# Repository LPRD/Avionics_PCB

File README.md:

# Avionics_PCB
EAGLE Board and schematic files

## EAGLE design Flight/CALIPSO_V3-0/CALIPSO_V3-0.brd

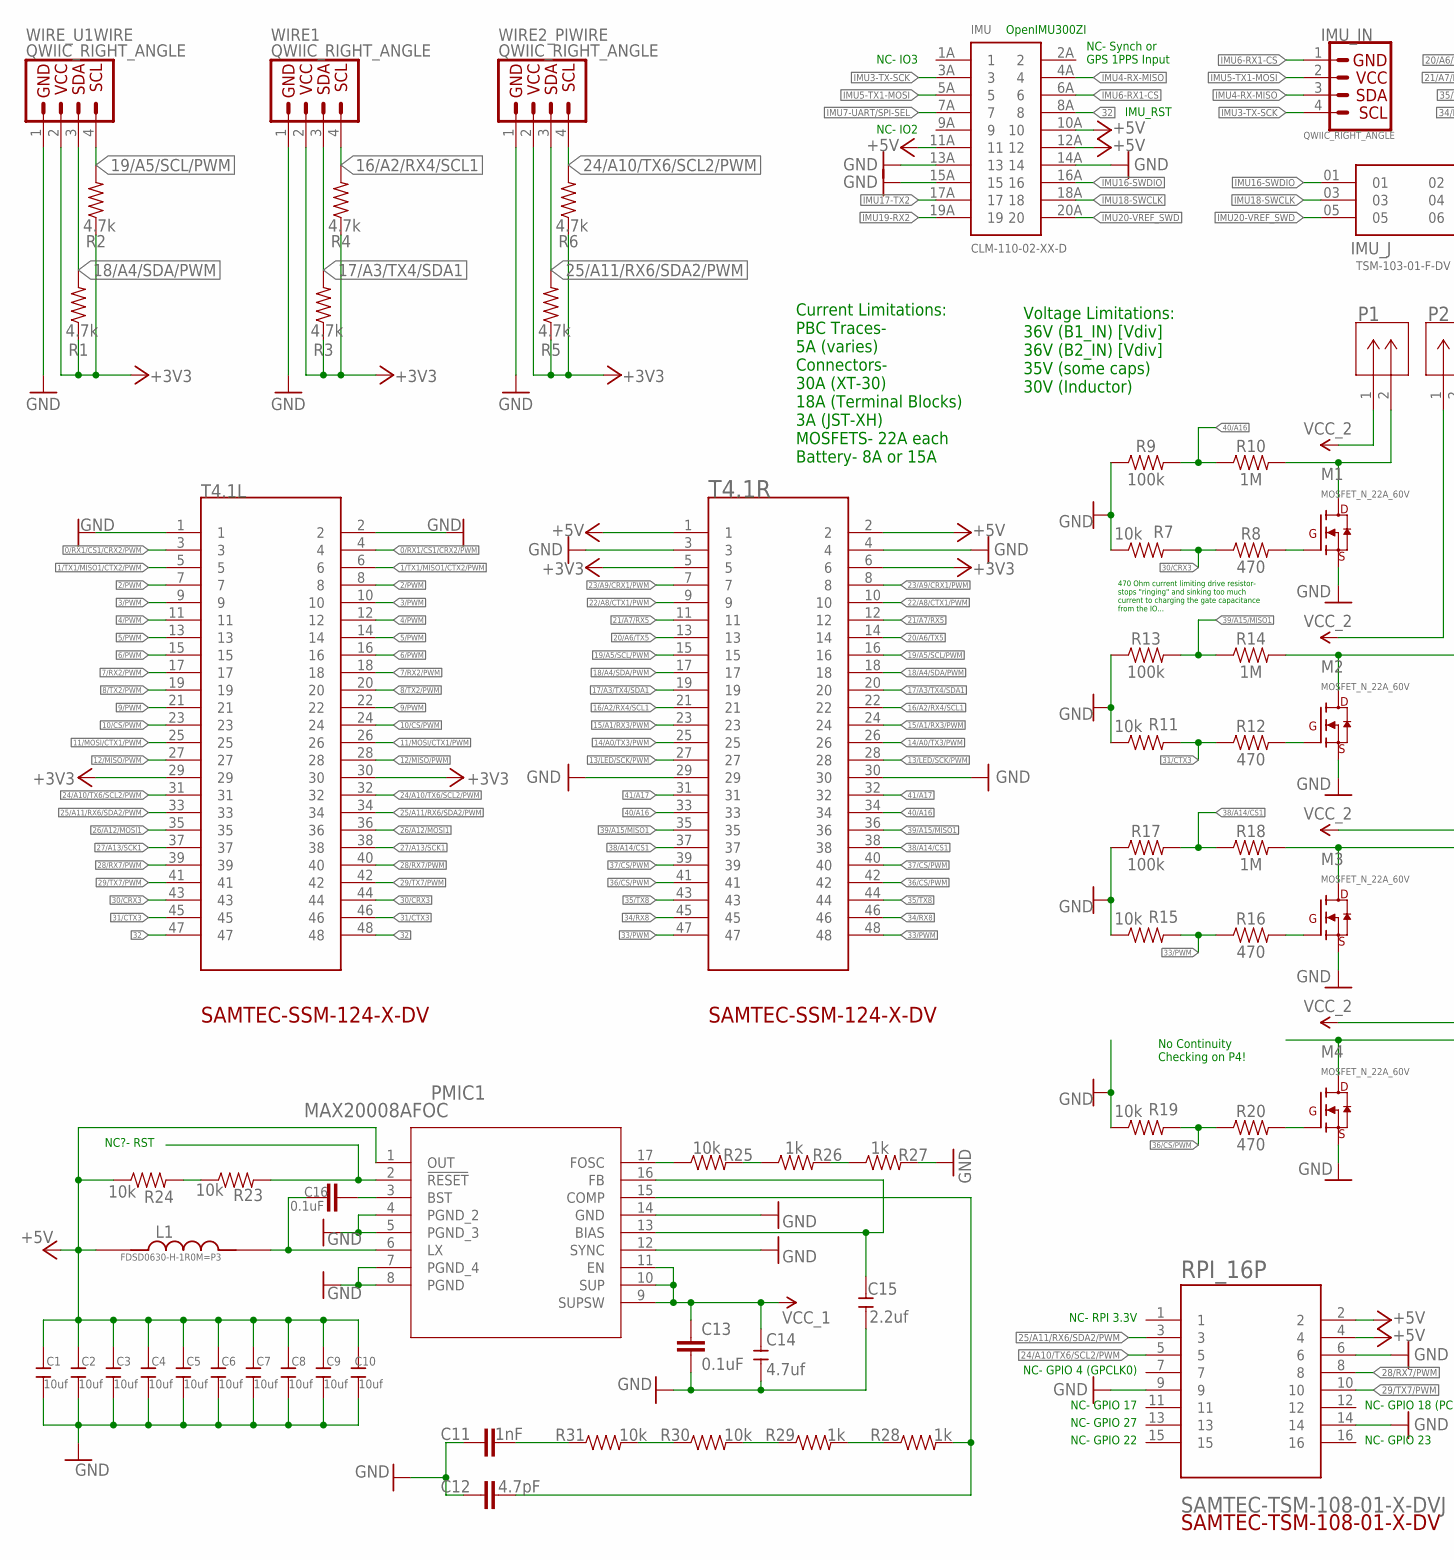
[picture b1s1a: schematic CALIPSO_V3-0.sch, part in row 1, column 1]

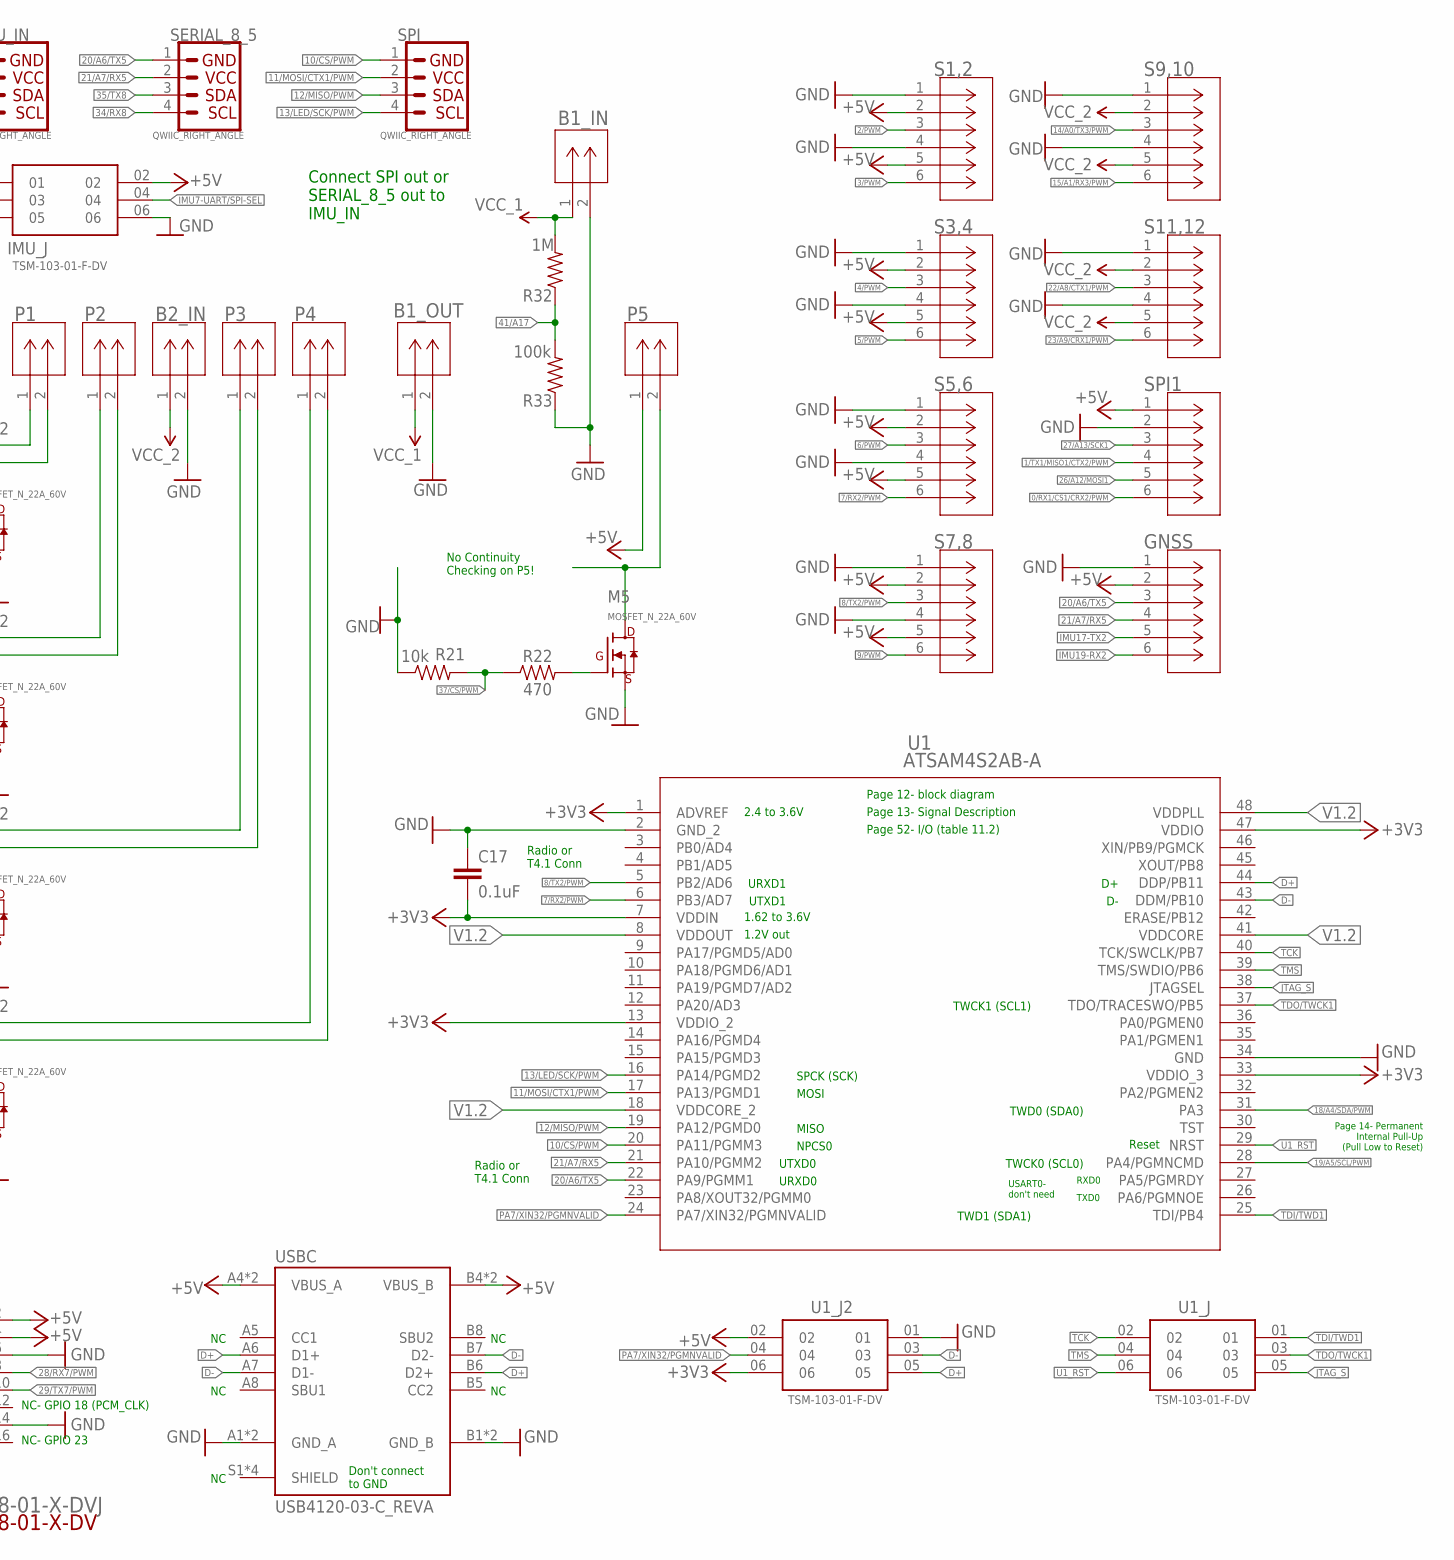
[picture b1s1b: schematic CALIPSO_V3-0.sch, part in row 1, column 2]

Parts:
B1_IN, B1_OUT, B2_IN: TERMINAL_BLOCK_5MM_2P; TB_2P
C1, C2, C3, C4, C5, C6, C7, C8, C9, C10: 10uf; C1206
C11: 1nF; 0603
C12: 4.7pF; 0603
C13, C16, C17: 0.1uF; 0603
C14: 4.7uf; C0805
C15: 2.2uf; C0805
GNSS: JST-S6B-SH_DEV; JST-S6B-XH
IMU: CLM-110-02-XX-D; CLM-110-02-XX-D_MOD
IMU_IN: QWIIC_RIGHT_ANGLE; JST04_1MM_RA
IMU_J: TSM-103-01-F-DV; SAMTEC_TSM-103-01-F-DV
L1: FDSD0630-H-1R0M=P3; IND_FDSD0630-H-1R0M=P3
M1, M2, M3, M4, M5: MOSFET_N_22A_60V; SOT-669_LFPAK56_POWERSO8
P1, P2, P3, P4, P5: TERMINAL_BLOCK_5MM_2P; TB_2P
PMIC1: MAX20008AFOC; MAX20008AFOC_17QFN
R1, R2, R3, R4, R5, R6: 4.7k; 0603
R7, R11, R15, R19, R21, R23, R24, R25, R30, R31: 10k; 0603
R8, R12, R16, R20, R22: 470; 0603
R9, R13, R17, R33: 100k; 0603
R10, R14, R18, R32: 1M; 0603
R26, R27, R28, R29: 1k; 0603
RPI_16P: SAMTEC-TSM-108-01-X-DVJ; SAMTEC-TSM-108-01-X-DV
S1,2, S3,4, S5,6, S7,8, S9,10, S11,12: JST-S6B-SH_DEV; JST-S6B-XH
SERIAL_8_5: QWIIC_RIGHT_ANGLE; JST04_1MM_RA
SPI: QWIIC_RIGHT_ANGLE; JST04_1MM_RA
SPI1: JST-S6B-SH_DEV; JST-S6B-XH
T4.1L, T4.1R: SAMTEC-SSM-124-X-DVJ; SAMTEC-SSM-124-X-DV
U1: ATSAM4S2AB-A; ATSAM4S2AB-A_48-LQFP
U1_J, U1_J2: TSM-103-01-F-DV; SAMTEC_TSM-103-01-F-DV
USBC: USB4120-03-C_REVA; GCT_USB4120-03-C_REVA
WIRE1, WIRE2_PIWIRE: QWIIC_RIGHT_ANGLE; JST04_1MM_RA
WIRE_U1WIRE: QWIIC_RIGHT_ANGLE; JST04_1MM_RA

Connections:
0/RX1/CS1/CRX2/PWM: SPI1.6, T4.1L.3, T4.1L.4
1/TX1/MISO1/CTX2/PWM: SPI1.4, T4.1L.5, T4.1L.6
2/PWM: S1,2.3, T4.1L.7, T4.1L.8
3/PWM: S1,2.6, T4.1L.9, T4.1L.10
4/PWM: S3,4.3, T4.1L.11, T4.1L.12
5/PWM: S3,4.6, T4.1L.13, T4.1L.14
6/PWM: S5,6.3, T4.1L.15, T4.1L.16
7/RX2/PWM: S5,6.6, T4.1L.17, T4.1L.18, U1.6 (PB3/AD7)
8/TX2/PWM: S7,8.3, T4.1L.19, T4.1L.20, U1.5 (PB2/AD6)
9/PWM: S7,8.6, T4.1L.21, T4.1L.22
10/CS/PWM: SPI.1, T4.1L.23, T4.1L.24, U1.20 (PA11/PGMM3)
11/MOSI/CTX1/PWM: SPI.2, T4.1L.25, T4.1L.26, U1.17 (PA13/PGMD1)
12/MISO/PWM: SPI.3, T4.1L.27, T4.1L.28, U1.19 (PA12/PGMD0)
13/LED/SCK/PWM: SPI.4, T4.1R.27, T4.1R.28, U1.16 (PA14/PGMD2)
14/A0/TX3/PWM: S9,10.3, T4.1R.25, T4.1R.26
15/A1/RX3/PWM: S9,10.6, T4.1R.23, T4.1R.24
16/A2/RX4/SCL1: R4.2, T4.1R.21, T4.1R.22, WIRE1.4
17/A3/TX4/SDA1: R3.2, T4.1R.19, T4.1R.20, WIRE1.3
18/A4/SDA/PWM: R1.2, T4.1R.17, T4.1R.18, U1.31 (PA3), WIRE_U1WIRE.3
19/A5/SCL/PWM: R2.2, T4.1R.15, T4.1R.16, U1.28 (PA4/PGMNCMD), WIRE_U1WIRE.4
20/A6/TX5: GNSS.3, SERIAL_8_5.1, T4.1R.13, T4.1R.14, U1.22 (PA9/PGMM1)
21/A7/RX5: GNSS.4, SERIAL_8_5.2, T4.1R.11, T4.1R.12, U1.21 (PA10/PGMM2)
22/A8/CTX1/PWM: S11,12.3, T4.1R.9, T4.1R.10
23/A9/CRX1/PWM: S11,12.6, T4.1R.7, T4.1R.8
24/A10/TX6/SCL2/PWM: R6.2, RPI_16P.5, T4.1L.31, T4.1L.32, WIRE2_PIWIRE.4
25/A11/RX6/SDA2/PWM: R5.2, RPI_16P.3, T4.1L.33, T4.1L.34, WIRE2_PIWIRE.3
26/A12/MOSI1: SPI1.5, T4.1L.35, T4.1L.36
27/A13/SCK1: SPI1.3, T4.1L.37, T4.1L.38
28/RX7/PWM: RPI_16P.8, T4.1L.39, T4.1L.40
29/TX7/PWM: RPI_16P.10, T4.1L.41, T4.1L.42
30/CRX3: R7.2, R8.1, T4.1L.43, T4.1L.44
31/CTX3: R11.2, R12.1, T4.1L.45, T4.1L.46
32: IMU.8A (8), T4.1L.47, T4.1L.48
33/PWM: R15.2, R16.1, T4.1R.47, T4.1R.48
34/RX8: SERIAL_8_5.4, T4.1R.45, T4.1R.46
35/TX8: SERIAL_8_5.3, T4.1R.43, T4.1R.44
36/CS/PWM: R19.2, R20.1, T4.1R.41, T4.1R.42
37/CS/PWM: R21.2, R22.1, T4.1R.39, T4.1R.40
38/A14/CS1: R17.2, R18.1, T4.1R.37, T4.1R.38
39/A15/MISO1: R13.2, R14.1, T4.1R.35, T4.1R.36
40/A16: R9.2, R10.1, T4.1R.33, T4.1R.34
41/A17: R32.1, R33.2, T4.1R.31, T4.1R.32
+3V3: C17.2, R1.1, R2.1, R3.1, R4.1, R5.1, R6.1, T4.1L.29, T4.1L.30, T4.1R.5, T4.1R.6, U1.1 (ADVREF), U1.7 (VDDIN), U1.13 (VDDIO_2), U1.33 (VDDIO_3), U1.47 (VDDIO), U1_J2.06, WIRE1.2, WIRE2_PIWIRE.2, WIRE_U1WIRE.2
+5V: C1.2, C2.2, C3.2, C4.2, C5.2, C6.2, C7.2, C8.2, C9.2, C10.2, GNSS.2, IMU.10A (10), IMU.11A (11), IMU.12A (12), IMU_J.02, L1.1, P5.1, PMIC1.1 (OUT), R24.1, RPI_16P.2, RPI_16P.4, S1,2.2, S1,2.5, S3,4.2, S3,4.5, S5,6.2, S5,6.5, S7,8.2, S7,8.5, SPI1.1, T4.1R.1, T4.1R.2, U1_J2.02, USBC.A4 (VBUS_A), USBC.A9 (VBUS_A), USBC.B4 (VBUS_B), USBC.B9 (VBUS_B)
BIAS/FB: C15.1, PMIC1.13 (BIAS), PMIC1.16 (FB)
BST: C16.2, PMIC1.3 (BST)
BUCK_RST: PMIC1.2 (!RESET), R23.2
COMP: C12.2, PMIC1.15 (COMP), R28.2
D+: U1.44 (DDP/PB11), U1_J2.05, USBC.A6 (D1+), USBC.B6 (D2+)
D-: U1.43 (DDM/PB10), U1_J2.03, USBC.A7 (D1-), USBC.B7 (D2-)
FOSC: PMIC1.17 (FOSC), R25.1
GND: B1_IN.2, B1_OUT.2, B2_IN.2, C1.1, C2.1, C3.1, C4.1, C5.1, C6.1, C7.1, C8.1, C9.1, C10.1, C11.1, C12.1, C13.2, C14.2, C15.2, C17.1, GNSS.1, IMU.13A (13), IMU.14A (14), IMU.15A (15), IMU_J.06, M1.1 (S), M1.2 (S), M1.3 (S), M2.1 (S), M2.2 (S), M2.3 (S), M3.1 (S), M3.2 (S), M3.3 (S), M4.1 (S), M4.2 (S), M4.3 (S), M5.1 (S), M5.2 (S), M5.3 (S), PMIC1.4 (PGND_2), PMIC1.5 (PGND_3), PMIC1.7 (PGND_4), PMIC1.8 (PGND), PMIC1.12 (SYNC), PMIC1.14 (GND), R7.1, R9.1, R11.1, R13.1, R15.1, R17.1, R19.1, R21.1, R27.2, R33.1, RPI_16P.6, RPI_16P.9, RPI_16P.14, S1,2.1, S1,2.4, S3,4.1, S3,4.4, S5,6.1, S5,6.4, S7,8.1, S7,8.4, S9,10.1, S9,10.4, S11,12.1, S11,12.4, SPI1.2, T4.1L.1, T4.1L.2, T4.1R.3, T4.1R.4, T4.1R.29, T4.1R.30, U1.2 (GND_2), U1.34 (GND), U1_J2.01, USBC.A1 (GND_A), USBC.A12 (GND_A), USBC.B1 (GND_B), USBC.B12 (GND_B), WIRE1.1, WIRE2_PIWIRE.1, WIRE_U1WIRE.1
IMU3-TX-SCK: IMU.3A (3), IMU_IN.4
IMU4-RX-MISO: IMU.4A (4), IMU_IN.3
IMU5-TX1-MOSI: IMU.5A (5), IMU_IN.2
IMU6-RX1-CS: IMU.6A (6), IMU_IN.1
IMU7-UART/SPI-SEL: IMU.7A (7), IMU_J.04
IMU16-SWDIO: IMU.16A (16), IMU_J.01
IMU17-TX2: GNSS.5, IMU.17A (17)
IMU18-SWCLK: IMU.18A (18), IMU_J.03
IMU19-RX2: GNSS.6, IMU.19A (19)
IMU20-VREF_SWD: IMU.20A (20), IMU_J.05
JTAG_S: U1.38 (JTAGSEL), U1_J.05
LX: C16.1, L1.2, PMIC1.6 (LX)
unnamed: M1.4 (G), R8.2
unnamed: M5.4 (G), R22.2
unnamed: R23.1, R24.2
unnamed: M2.4 (G), R12.2
unnamed: R25.2, R26.1
unnamed: R26.2, R27.1
unnamed: R30.1, R31.2
unnamed: R29.1, R30.2
unnamed: R28.1, R29.2
unnamed: M3.4 (G), R16.2
unnamed: C11.2, R31.1
unnamed: M4.4 (G), R20.2
P1D: M1.5 (D), P1.2, R10.2
P2D: M2.5 (D), P2.2, R14.2
P3D: M3.5 (D), P3.2, R18.2
P4D: M4.5 (D), P4.2
P5D: M5.5 (D), P5.2
PA7/XIN32/PGMNVALID: U1.24 (PA7/XIN32/PGMNVALID), U1_J2.04
TCK: U1.40 (TCK/SWCLK/PB7), U1_J.02
TDI/TWD1: U1.25 (TDI/PB4), U1_J.01
TDO/TWCK1: U1.37 (TDO/TRACESWO/PB5), U1_J.03
TMS: U1.39 (TMS/SWDIO/PB6), U1_J.04
U1_RST: U1.29 (NRST), U1_J.06
V1.2: U1.8 (VDDOUT), U1.18 (VDDCORE_2), U1.41 (VDDCORE), U1.48 (VDDPLL)
VCC_1: B1_IN.1, B1_OUT.1, C13.1, C14.1, PMIC1.9 (SUPSW), PMIC1.10 (SUP), PMIC1.11 (EN), R32.2
VCC_2: B2_IN.1, P1.1, P2.1, P3.1, P4.1, S9,10.2, S9,10.5, S11,12.2, S11,12.5

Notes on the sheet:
Current Limitations: PBC Traces- 5A (varies) Connectors- 30A (XT-30) 18A (Terminal Blocks) 3A (JST-XH) MOSFETS- 22A each Battery- 8A or 15A
470 Ohm current limiting drive resistor- stops "ringing" and sinking too much current to charging the gate capacitance from the IO...
Connect SPI out or SERIAL_8_5 out to IMU_IN
IMU_RST
NC- Synch or GPS 1PPS Input
NC- IO3
NC- IO2
NC- RPI 3.3V
NC- GPIO 4 (GPCLK0)
NC- GPIO 17
NC- GPIO 27
NC- GPIO 22
NC- GPIO 18 (PCM_CLK)
NC- GPIO 23
No Continuity Checking on P4!
No Continuity Checking on P5!
NC?- RST
Voltage Limitations: 36V (B1_IN) [Vdiv] 36V (B2_IN) [Vdiv] 35V (some caps) 30V (Inductor)
2.4 to 3.6V
1.2V out
1.62 to 3.6V
Reset
Page 52- I/O (table 11.2)
RXD0
TXD0
URXD0
UTXD0
URXD1
UTXD1
Page 12- block diagram
USART0- don't need
TWD0 (SDA0)
TWCK0 (SCL0)
TWD1 (SDA1)
TWCK1 (SCL1)
NPCS0
MISO
MOSI
SPCK (SCK)
Page 13- Signal Description

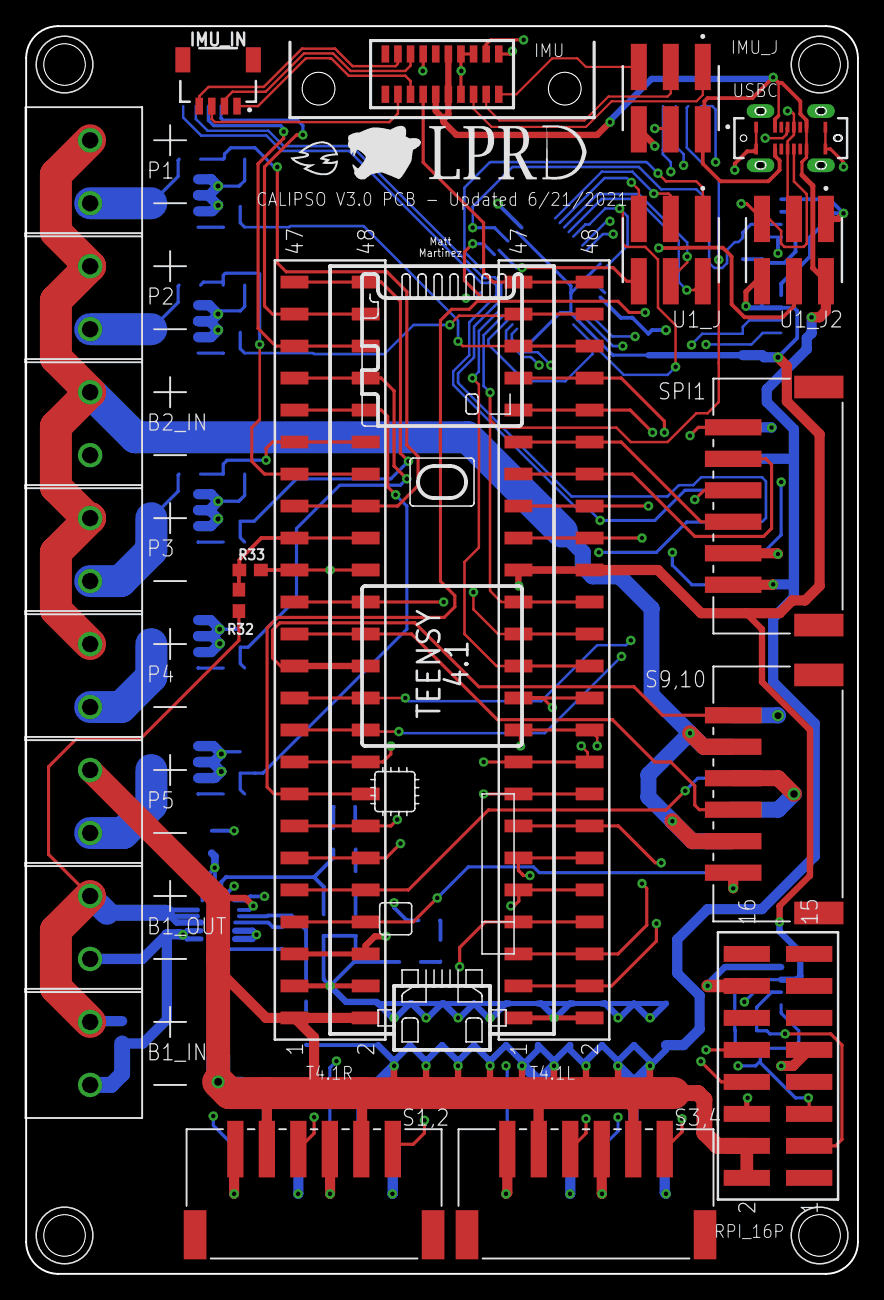
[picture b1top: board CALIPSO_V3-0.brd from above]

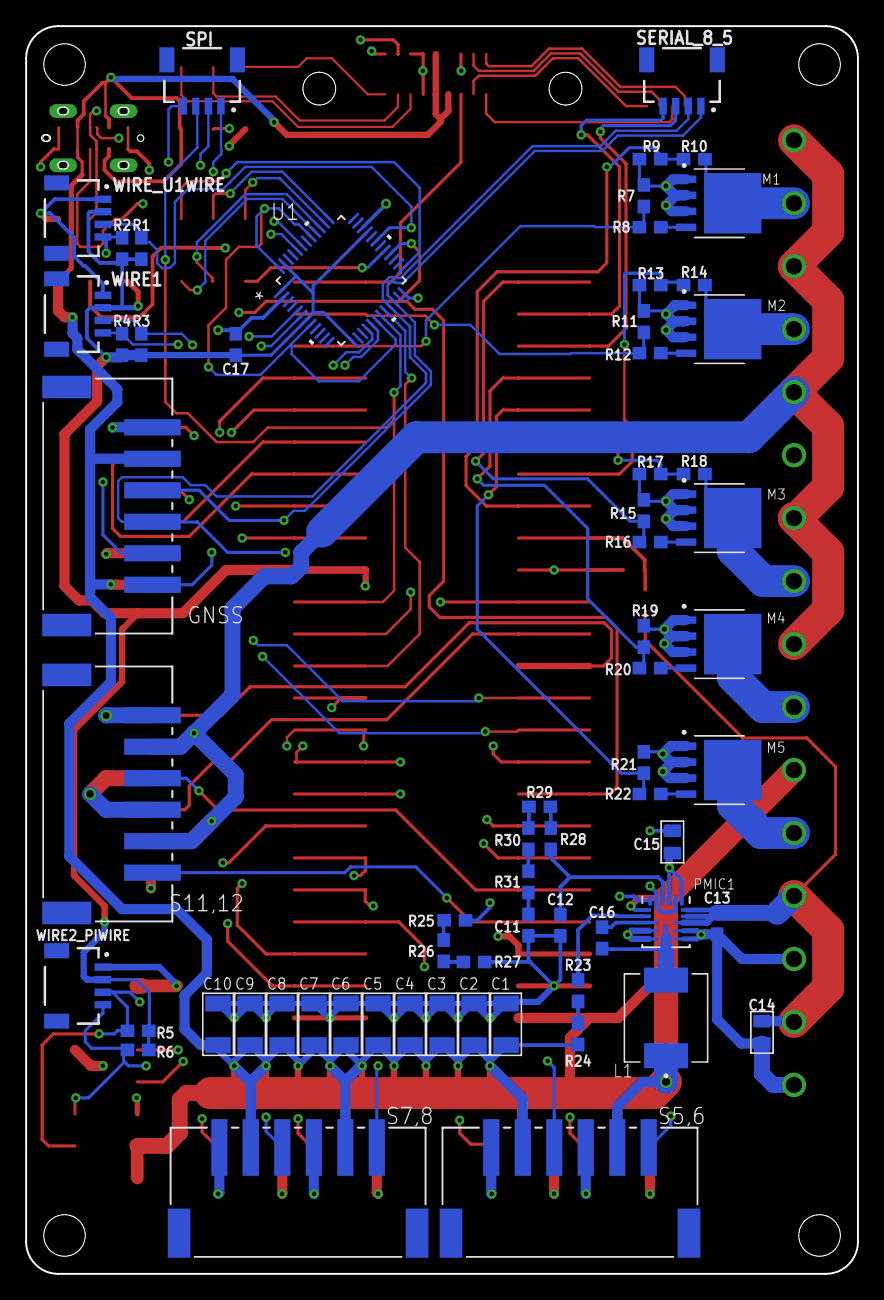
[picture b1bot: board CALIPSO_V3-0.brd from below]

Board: 4 copper layers, 66.0 x 99.1 mm, 89 parts (65 on the bottom side), 90 nets.

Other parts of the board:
U$1: TEENSY_4.1_SILKSCREEN

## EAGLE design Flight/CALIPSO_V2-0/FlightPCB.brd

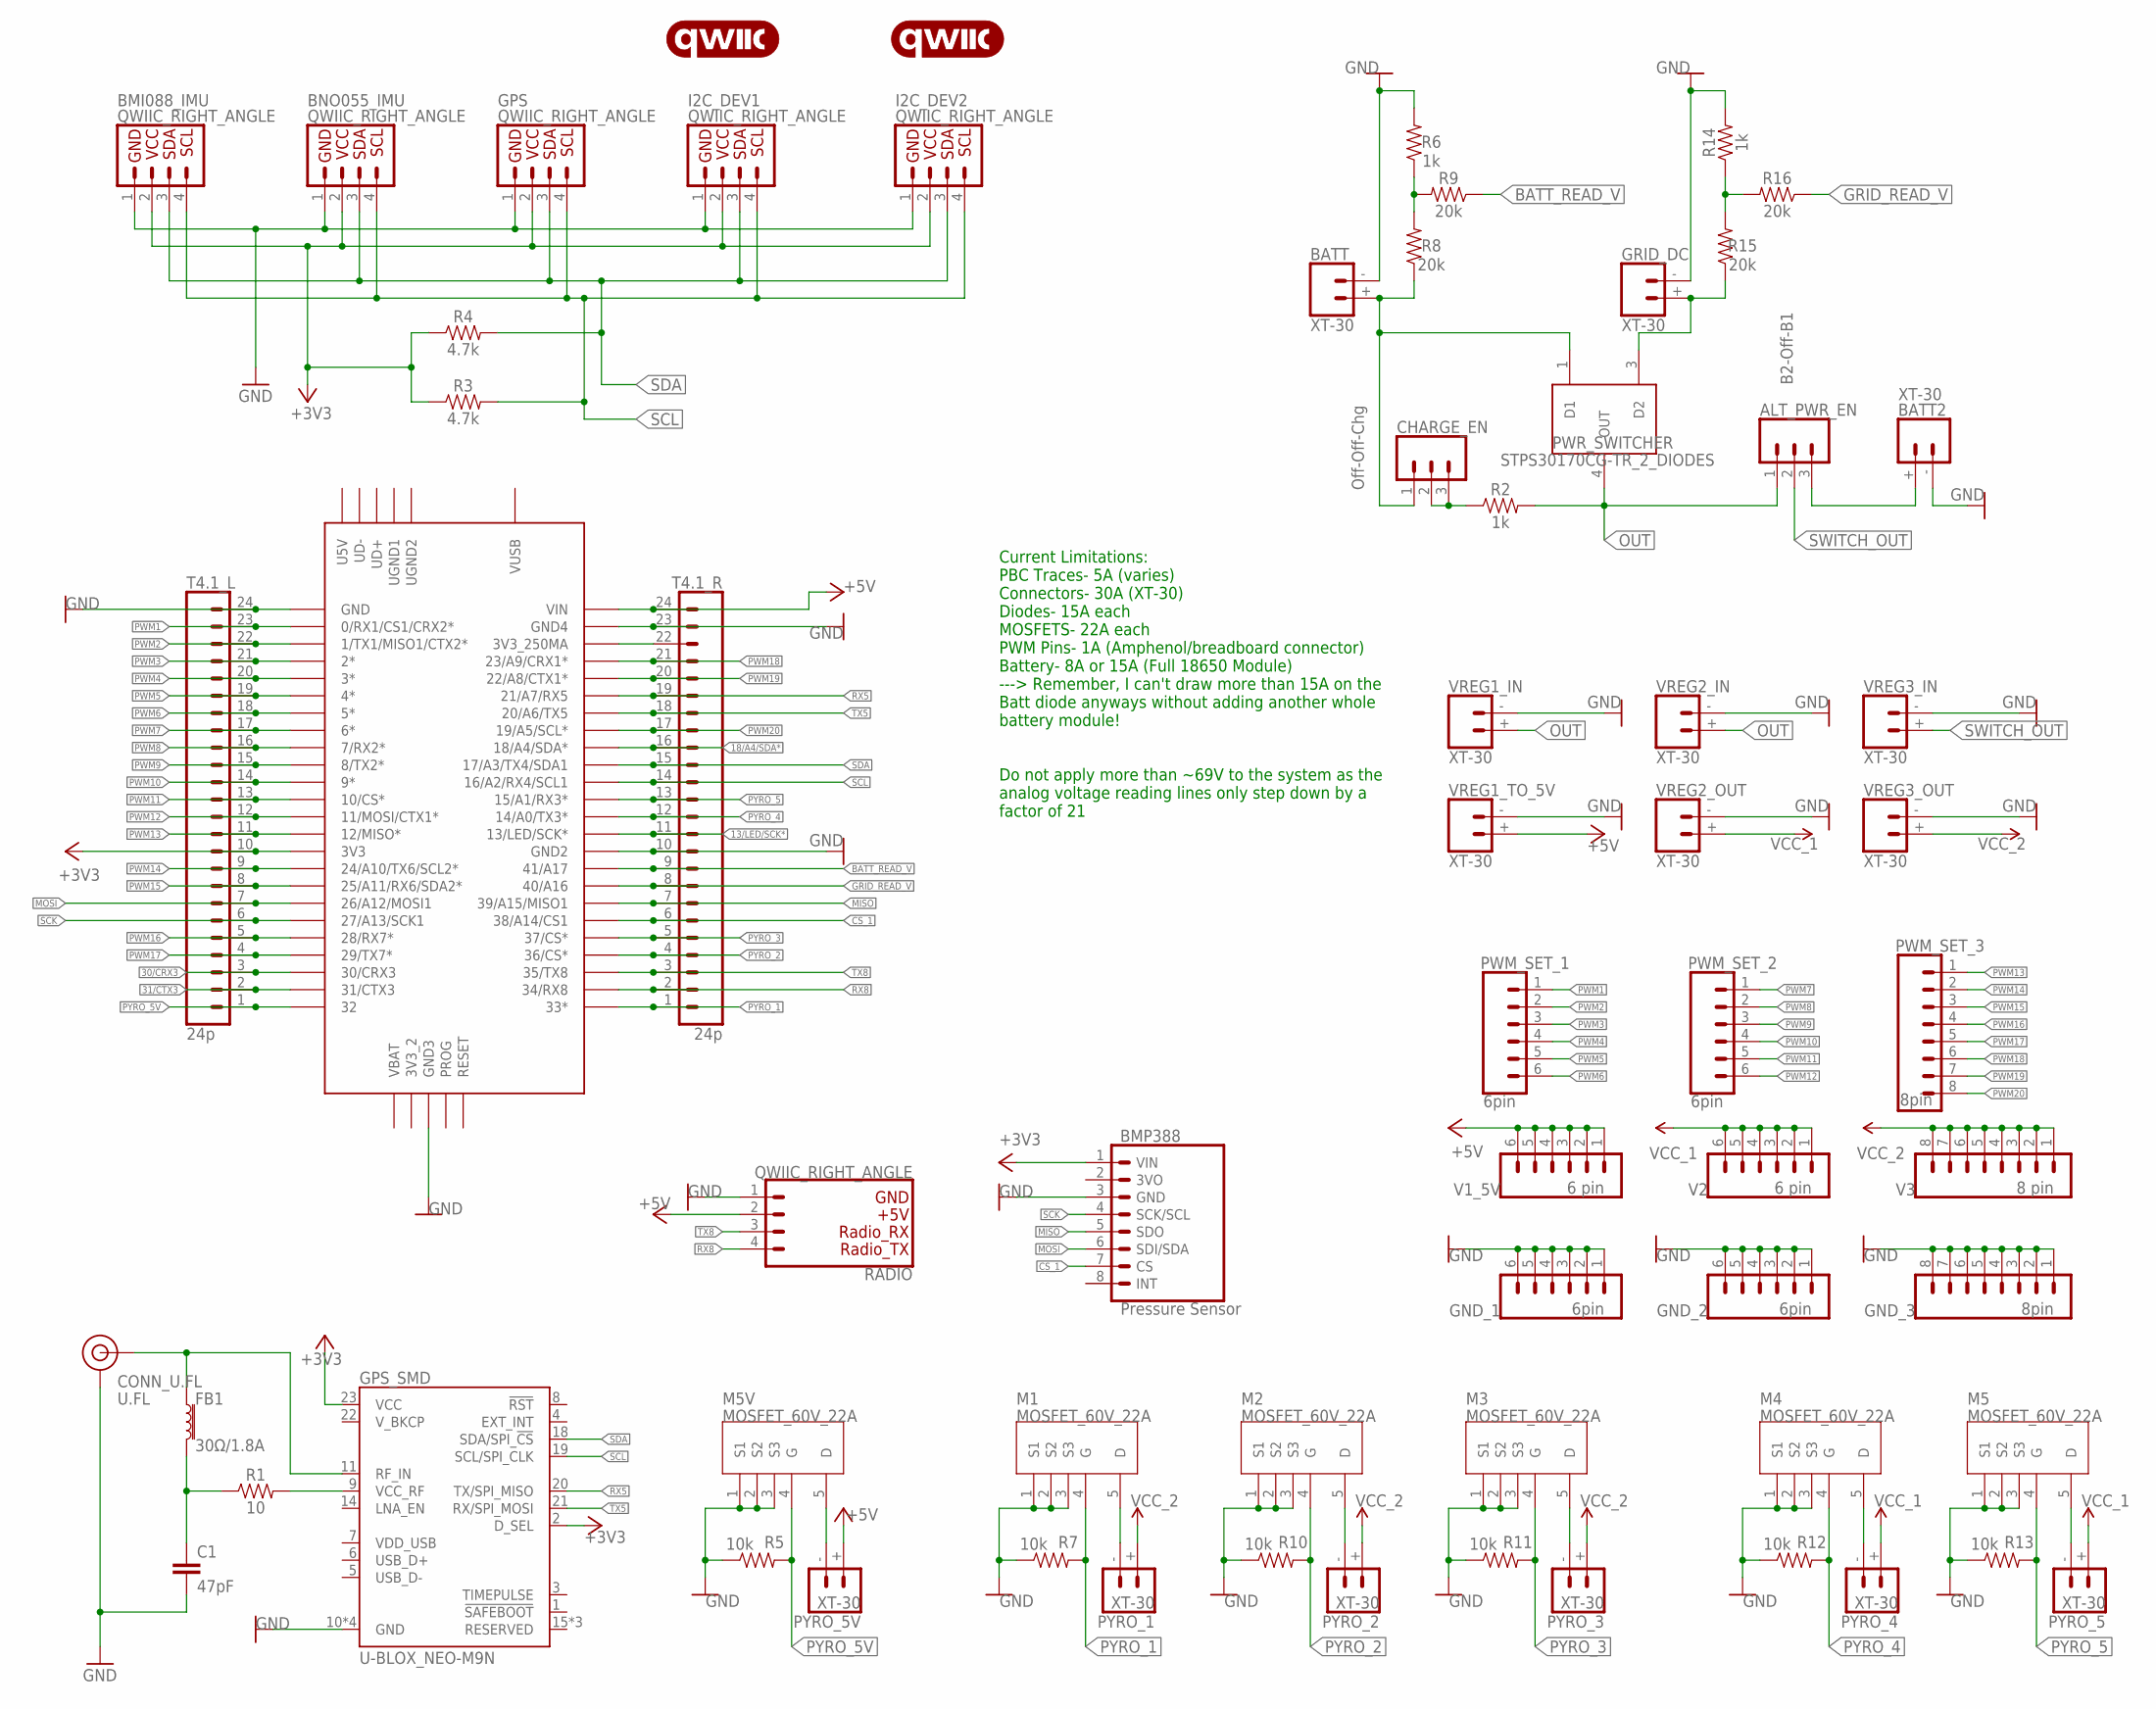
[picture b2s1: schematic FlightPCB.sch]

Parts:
ALT_PWR_EN: B2-Off-B1; 1X03_SLIDE_SWITCH_EG5137
BATT, BATT2: XT-30; 1X02_BIG_XT-30
BMI088_IMU: QWIIC_RIGHT_ANGLE; JST04_1MM_RA
BMP388: Pressure Sensor; 1X08_FEMALE_LOCK
BNO055_IMU: QWIIC_RIGHT_ANGLE; JST04_1MM_RA
C1: 47pF; 0603
CHARGE_EN: Off-Off-Chg; 1X03_SLIDE_SWITCH_EG5137
CONN_U.FL: U.FL
FB1: 30Ω/1.8A; 0603
GND_1, GND_2: 6pin; 1X06_LOCK
GND_3: 8pin; 1X08_LOCK
GPS: QWIIC_RIGHT_ANGLE; JST04_1MM_RA
GPS_SMD: U-BLOX_NEO-M9N; NEO-M9N/M8T/M8U
GRID_DC: XT-30; 1X02_BIG_XT-30
I2C_DEV1, I2C_DEV2: QWIIC_RIGHT_ANGLE; JST04_1MM_RA
LOGO1, LOGO2: QWIIC_LOGO_CONNECTOR; QWIIC_5.5MM
M1, M2, M3, M4, M5, M5V: MOSFET_60V_22A; TO127P600X120-5N
PWM_SET_1, PWM_SET_2: 6pin; 1X06_LOCK
PWM_SET_3: 8pin; 1X08_LOCK
PWR_SWITCHER: STPS30170CG-TR_2_DIODES; TO-263-3_PACKAGE_MIDDLE_PIN_REMOVED
PYRO_1, PYRO_2, PYRO_3, PYRO_4, PYRO_5, PYRO_5V: XT-30; 1X02_BIG_XT-30
R1: 10; 0603
R2, R6, R14: 1k; 0603
R3, R4: 4.7k; 0603
R5, R7, R10, R11, R12, R13: 10k; 0603
R8, R9, R15, R16: 20k; 0603
RADIO: QWIIC_RIGHT_ANGLE; JST04_1MM_RA
T4.1_L, T4.1_R: 24p; 1X24_LOCK
TEENSY_4.1: TEENSY_4.1
V1_5V, V2: 6 pin; 1X06_LOCK
V3: 8 pin; 1X08_LOCK
VREG1_IN, VREG1_TO_5V, VREG2_IN, VREG2_OUT, VREG3_IN, VREG3_OUT: XT-30; 1X02_BIG_XT-30

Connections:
13/LED/SCK*: T4.1_R.11, TEENSY_4.1.13/LED/SCK*
18/A4/SDA*: T4.1_R.16, TEENSY_4.1.18/A4/SDA*
30/CRX3: T4.1_L.3, TEENSY_4.1.30/CRX3
31/CTX3: T4.1_L.2, TEENSY_4.1.31/CTX3
+3V3: BMI088_IMU.2, BMP388.1 (VIN), BNO055_IMU.2, GPS.2, GPS_SMD.2 (D_SEL), GPS_SMD.23 (VCC), I2C_DEV1.2, I2C_DEV2.2, R3.1, R4.1, T4.1_L.10, TEENSY_4.1.3V3
+5V: PYRO_5V.+, RADIO.2, T4.1_R.24, TEENSY_4.1.VIN, V1_5V.1, V1_5V.2, V1_5V.3, V1_5V.4, V1_5V.5, V1_5V.6, VREG1_TO_5V.+
BATT_READ_V: R9.1, T4.1_R.9, TEENSY_4.1.41/A17
CS_1: BMP388.7 (CS), T4.1_R.6, TEENSY_4.1.38/A14/CS1
GND: BATT.-, BATT2.-, BMI088_IMU.1, BMP388.3 (GND), BNO055_IMU.1, C1.2, CONN_U.FL.1 (GND), CONN_U.FL.2 (GND), GND_1.1, GND_1.2, GND_1.3, GND_1.4, GND_1.5, GND_1.6, GND_2.1, GND_2.2, GND_2.3, GND_2.4, GND_2.5, GND_2.6, GND_3.1, GND_3.2, GND_3.3, GND_3.4, GND_3.5, GND_3.6, GND_3.7, GND_3.8, GPS.1, GPS_SMD.10 (GND), GPS_SMD.12 (GND), GPS_SMD.13 (GND), GPS_SMD.24 (GND), GRID_DC.-, I2C_DEV1.1, I2C_DEV2.1, M1.1 (S1), M1.2 (S2), M1.3 (S3), M2.1 (S1), M2.2 (S2), M2.3 (S3), M3.1 (S1), M3.2 (S2), M3.3 (S3), M4.1 (S1), M4.2 (S2), M4.3 (S3), M5.1 (S1), M5.2 (S2), M5.3 (S3), M5V.1 (S1), M5V.2 (S2), M5V.3 (S3), R5.1, R6.2, R7.1, R10.1, R11.1, R12.1, R13.1, R14.2, RADIO.1, T4.1_L.24, T4.1_R.10, T4.1_R.23, TEENSY_4.1.GND, TEENSY_4.1.GND2, TEENSY_4.1.GND3, TEENSY_4.1.GND4, VREG1_IN.-, VREG1_TO_5V.-, VREG2_IN.-, VREG2_OUT.-, VREG3_IN.-, VREG3_OUT.-
GRID_READ_V: R16.1, T4.1_R.8, TEENSY_4.1.40/A16
MISO: BMP388.5 (SDO), T4.1_R.7, TEENSY_4.1.39/A15/MISO1
MOSI: BMP388.6 (SDI/SDA), T4.1_L.7, TEENSY_4.1.26/A12/MOSI1
unnamed: CONN_U.FL.FEED (SIGNAL), FB1.1, GPS_SMD.11 (RF_IN)
unnamed: C1.1, FB1.2, R1.1
unnamed: GPS_SMD.9 (VCC_RF), R1.2
unnamed: CHARGE_EN.2, CHARGE_EN.3, R2.1
unnamed: ALT_PWR_EN.3, BATT2.+
unnamed: R6.1, R8.2, R9.2
unnamed: M5V.5 (D), PYRO_5V.-
unnamed: GRID_DC.+, PWR_SWITCHER.3 (D2), R15.1
unnamed: M1.5 (D), PYRO_1.-
unnamed: M2.5 (D), PYRO_2.-
unnamed: M3.5 (D), PYRO_3.-
unnamed: M4.5 (D), PYRO_4.-
unnamed: M5.5 (D), PYRO_5.-
unnamed: BATT.+, CHARGE_EN.1, PWR_SWITCHER.1 (D1), R8.1
unnamed: R14.1, R15.2, R16.2
unnamed: T4.1_R.22, TEENSY_4.1.3V3_250MA
OUT: ALT_PWR_EN.1, PWR_SWITCHER.4 (OUT), R2.2, VREG1_IN.+, VREG2_IN.+
PWM1: PWM_SET_1.1, T4.1_L.23, TEENSY_4.1.0/RX1/CS1/CRX2*
PWM2: PWM_SET_1.2, T4.1_L.22, TEENSY_4.1.1/TX1/MISO1/CTX2*
PWM3: PWM_SET_1.3, T4.1_L.21, TEENSY_4.1.2*
PWM4: PWM_SET_1.4, T4.1_L.20, TEENSY_4.1.3*
PWM5: PWM_SET_1.5, T4.1_L.19, TEENSY_4.1.4*
PWM6: PWM_SET_1.6, T4.1_L.18, TEENSY_4.1.5*
PWM7: PWM_SET_2.1, T4.1_L.17, TEENSY_4.1.6*
PWM8: PWM_SET_2.2, T4.1_L.16, TEENSY_4.1.7/RX2*
PWM9: PWM_SET_2.3, T4.1_L.15, TEENSY_4.1.8/TX2*
PWM10: PWM_SET_2.4, T4.1_L.14, TEENSY_4.1.9*
PWM11: PWM_SET_2.5, T4.1_L.13, TEENSY_4.1.10/CS*
PWM12: PWM_SET_2.6, T4.1_L.12, TEENSY_4.1.11/MOSI/CTX1*
PWM13: PWM_SET_3.1, T4.1_L.11, TEENSY_4.1.12/MISO*
PWM14: PWM_SET_3.2, T4.1_L.9, TEENSY_4.1.24/A10/TX6/SCL2*
PWM15: PWM_SET_3.3, T4.1_L.8, TEENSY_4.1.25/A11/RX6/SDA2*
PWM16: PWM_SET_3.4, T4.1_L.5, TEENSY_4.1.28/RX7*
PWM17: PWM_SET_3.5, T4.1_L.4, TEENSY_4.1.29/TX7*
PWM18: PWM_SET_3.6, T4.1_R.21, TEENSY_4.1.23/A9/CRX1*
PWM19: PWM_SET_3.7, T4.1_R.20, TEENSY_4.1.22/A8/CTX1*
PWM20: PWM_SET_3.8, T4.1_R.17, TEENSY_4.1.19/A5/SCL*
PYRO_1: M1.4 (G), R7.2, T4.1_R.1, TEENSY_4.1.33*
PYRO_2: M2.4 (G), R10.2, T4.1_R.4, TEENSY_4.1.36/CS*
PYRO_3: M3.4 (G), R11.2, T4.1_R.5, TEENSY_4.1.37/CS*
PYRO_4: M4.4 (G), R12.2, T4.1_R.12, TEENSY_4.1.14/A0/TX3*
PYRO_5: M5.4 (G), R13.2, T4.1_R.13, TEENSY_4.1.15/A1/RX3*
PYRO_5V: M5V.4 (G), R5.2, T4.1_L.1, TEENSY_4.1.32
RX5: GPS_SMD.20 (TX/SPI_MISO), T4.1_R.19, TEENSY_4.1.21/A7/RX5
RX8: RADIO.4, T4.1_R.2, TEENSY_4.1.34/RX8
SCK: BMP388.4 (SCK/SCL), T4.1_L.6, TEENSY_4.1.27/A13/SCK1
SCL: BMI088_IMU.4, BNO055_IMU.4, GPS.4, GPS_SMD.19 (SCL/SPI_CLK), I2C_DEV1.4, I2C_DEV2.4, R3.2, T4.1_R.14, TEENSY_4.1.16/A2/RX4/SCL1
SDA: BMI088_IMU.3, BNO055_IMU.3, GPS.3, GPS_SMD.18 (SDA/SPI_!CS!), I2C_DEV1.3, I2C_DEV2.3, R4.2, T4.1_R.15, TEENSY_4.1.17/A3/TX4/SDA1
SWITCH_OUT: ALT_PWR_EN.2, VREG3_IN.+
TX5: GPS_SMD.21 (RX/SPI_MOSI), T4.1_R.18, TEENSY_4.1.20/A6/TX5
TX8: RADIO.3, T4.1_R.3, TEENSY_4.1.35/TX8
VCC_1: PYRO_4.+, PYRO_5.+, V2.1, V2.2, V2.3, V2.4, V2.5, V2.6, VREG2_OUT.+
VCC_2: PYRO_1.+, PYRO_2.+, PYRO_3.+, V3.1, V3.2, V3.3, V3.4, V3.5, V3.6, V3.7, V3.8, VREG3_OUT.+

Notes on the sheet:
Current Limitations: PBC Traces- 5A (varies) Connectors- 30A (XT-30) Diodes- 15A each MOSFETS- 22A each PWM Pins- 1A (Amphenol/breadboard connector) Battery- 8A or 15A (Full 18650 Module) ---> Remember, I can't draw more than 15A on the Batt diode anyways without adding another whole battery module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

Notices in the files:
parts and their libraries:
MODIFIED-SparkFun-Connectors: Licensing: Creative Commons ShareAlike 4.0 International - https://creativecommons.org/licenses/by-sa/4.0
